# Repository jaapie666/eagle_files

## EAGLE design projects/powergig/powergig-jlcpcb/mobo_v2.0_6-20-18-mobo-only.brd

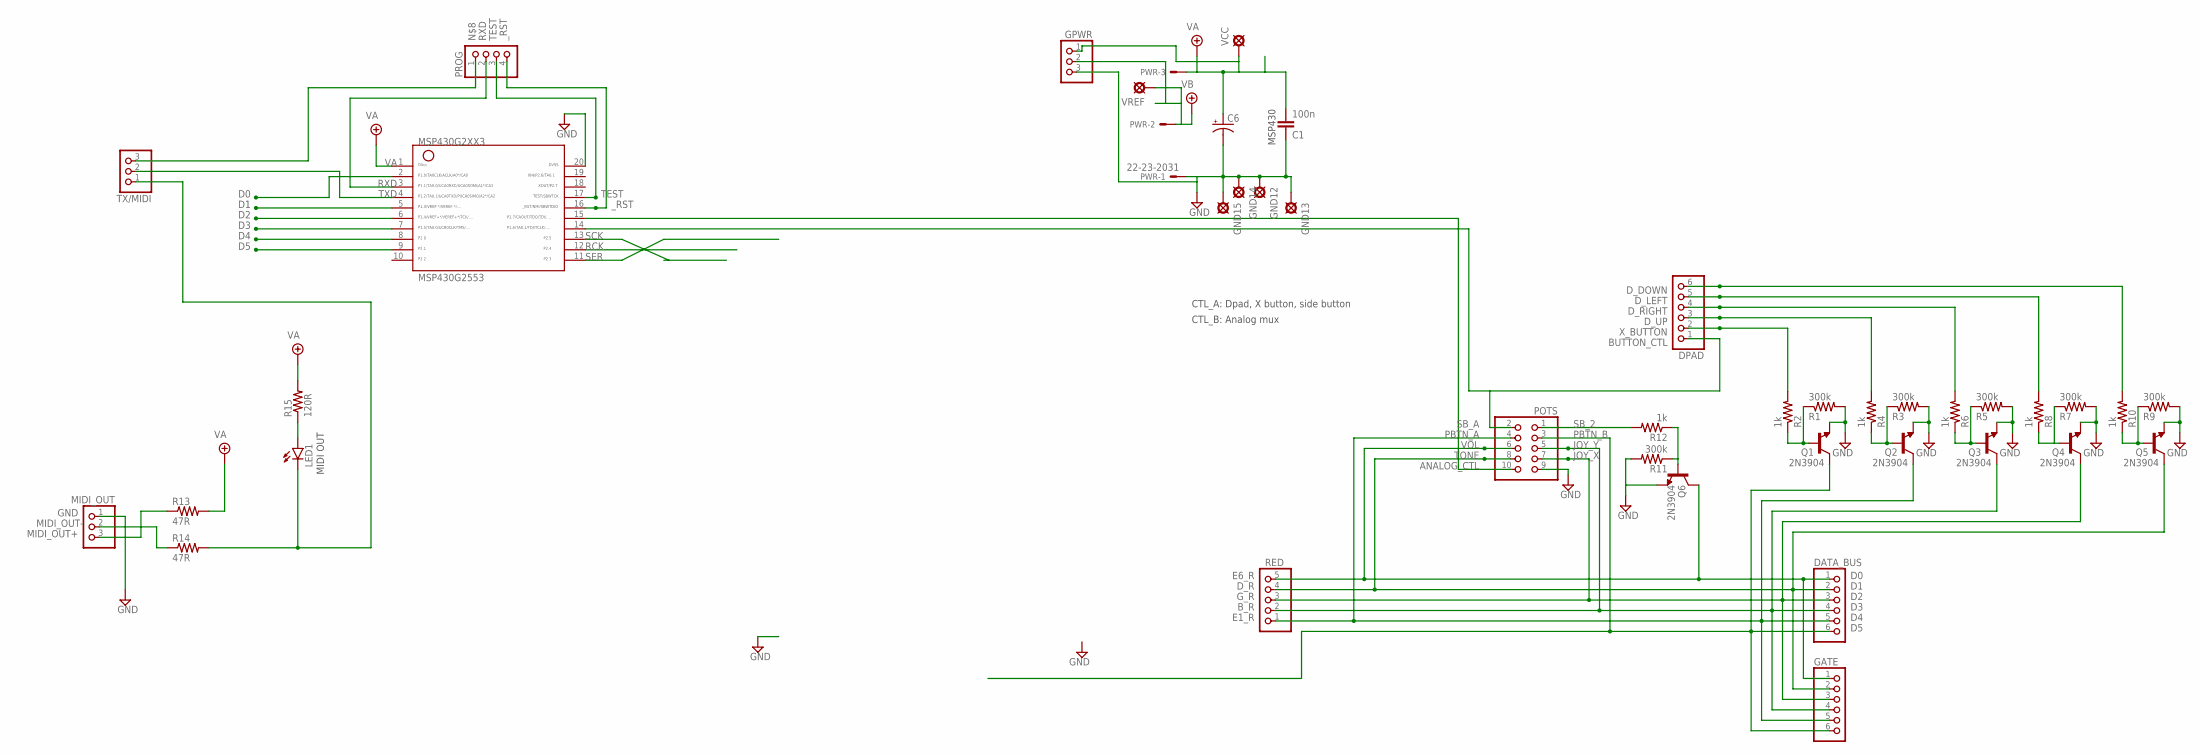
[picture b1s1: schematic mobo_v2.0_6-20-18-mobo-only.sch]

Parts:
C1: 100n; 050X030_050_3
C6: 0501; 050_020_1
DATA_BUS: PINHD-1X6; 1X06
DPAD: PINHD-1X6; 1X06
GATE: PINHD-1X6; 1X06
GND12, GND13, GND14, GND15: PAD; SQUARE
GPWR: PINHD-1X3; 1X03
LED1: LED3MM
MIDI_OUT: PINHD-1X3; 1X03
MSP430G2553: G2XX3---N20; N20
POTS: PINHD-2X5IDC; 10PIN_IDC
PROG: PINHD-1X4; 1X04
PWR: 22-23-2031
Q1, Q2, Q3, Q4, Q5, Q6: 2N3904; TO92-
R1, R3, R5, R7, R9, R11: 300k; R0207/3
R2, R4, R6, R8, R10, R12: 1k; R0207/3
R13, R14: 47R; R0207/3
R15: 120R; R0207/3
RED: PINHD-1X5; 1X05
TX/MIDI: PINHD-1X3; 1X03
VCC: PAD; SQUARE
VREF: PAD; SQUARE

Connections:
ANALOG_CTL: MSP430G2553.15, POTS.10
BUTTON_CTL: DPAD.1, MSP430G2553.14, POTS.2
D0: DATA_BUS.1, GATE.1, MSP430G2553.2, POTS.6, Q6.1 (C), RED.5
D1: DATA_BUS.2, GATE.2, MSP430G2553.5, POTS.8, Q5.1 (C), RED.4
D2: DATA_BUS.3, GATE.3, MSP430G2553.6, POTS.7, Q4.1 (C), RED.3
D3: DATA_BUS.4, GATE.4, MSP430G2553.7, POTS.5, Q3.1 (C), RED.2
D4: DATA_BUS.5, GATE.5, MSP430G2553.8, POTS.4, Q2.1 (C), RED.1
D5: DATA_BUS.6, GATE.6, MSP430G2553.9, POTS.3, Q1.1 (C)
D_DOWN: DPAD.6, R10.2
D_LEFT: DPAD.5, R8.2
D_RIGHT: DPAD.4, R6.2
D_UP: DPAD.3, R4.2
GND: C1.1, C6.-, GND12.1, GND13.1, GND14.1, GND15.1, GPWR.3, MIDI_OUT.1, MSP430G2553.20, POTS.9, PWR.1, Q1.3 (E), Q2.3 (E), Q3.3 (E), Q4.3 (E), Q5.3 (E), Q6.3 (E), R1.2, R3.2, R5.2, R7.2, R9.2, R11.2
MIDI_OUT+: MIDI_OUT.3, R13.1
MIDI_OUT-: MIDI_OUT.2, R14.1
unnamed: Q6.2 (B), R11.1, R12.1
unnamed: LED1.A, R15.1
unnamed: LED1.K (C), R14.2, TX/MIDI.1
unnamed: PROG.1, TX/MIDI.3
unnamed: Q1.2 (B), R1.1, R2.1
unnamed: Q2.2 (B), R3.1, R4.1
unnamed: Q3.2 (B), R5.1, R6.1
unnamed: Q4.2 (B), R7.1, R8.1
unnamed: Q5.2 (B), R9.1, R10.1
RCK: MSP430G2553.12
RXD: MSP430G2553.3, PROG.2
SB_2: POTS.1, R12.2
SCK: MSP430G2553.13
SER: MSP430G2553.11
TEST: MSP430G2553.17, PROG.3
TXD: MSP430G2553.4, TX/MIDI.2
VA: C1.2, C6.+, GPWR.1, MSP430G2553.1, PWR.3, R13.2, R15.2, VCC.1
VB: GPWR.2, PWR.2, VREF.1
X_BUTTON: DPAD.2, R2.2
_RST: MSP430G2553.16, PROG.4

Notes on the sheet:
MSP430
E6_R
D_R
G_R
B_R
E1_R
TONE
VOL
PBTN_A
PBTN_B
JOY_X
JOY_Y
SB_A
CTL_A: Dpad, X button, side button
CTL_B: Analog mux
MIDI OUT

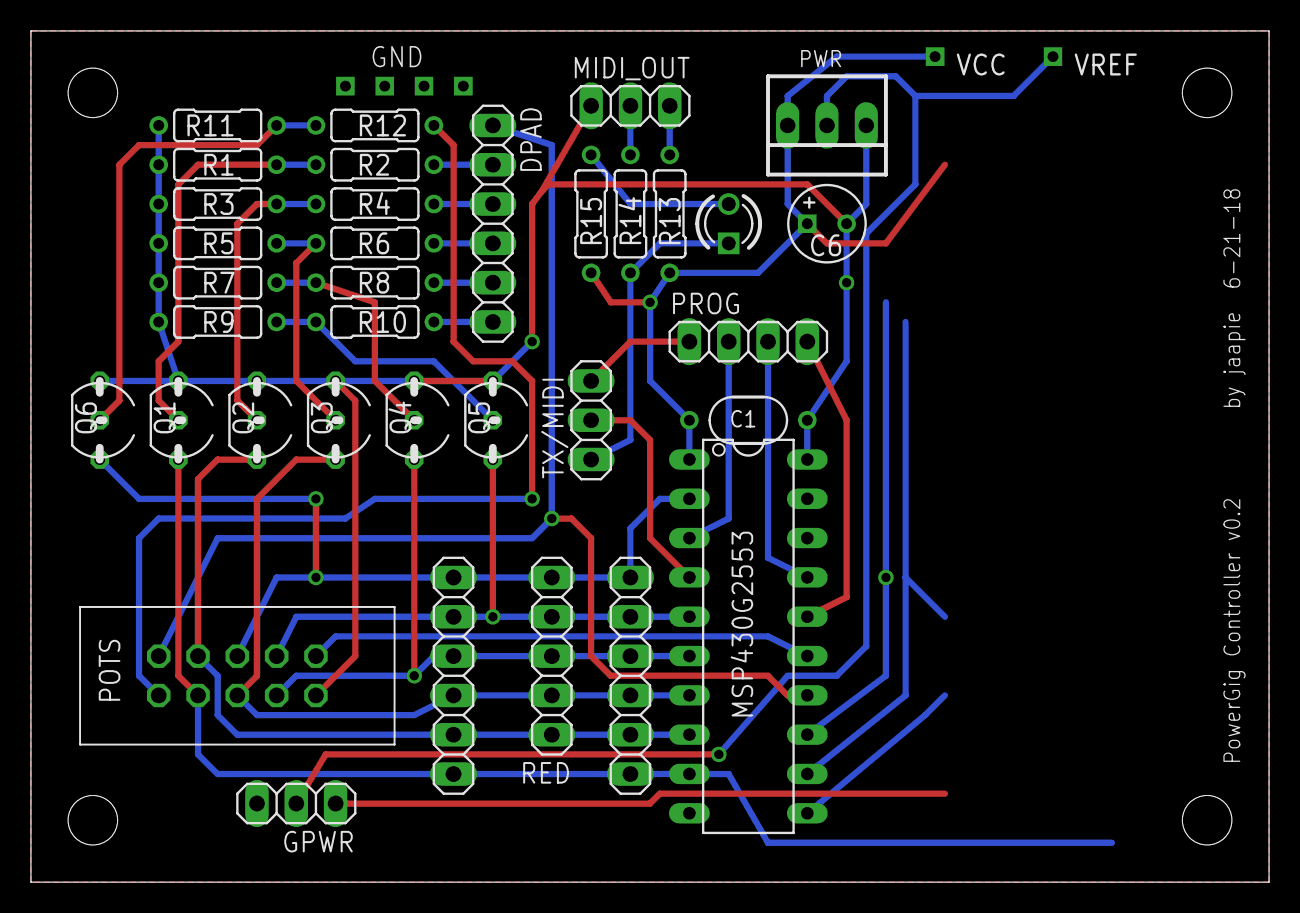
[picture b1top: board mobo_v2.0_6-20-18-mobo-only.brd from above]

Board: 2 copper layers, 80.0 x 55.0 mm, 41 parts (0 on the bottom side), 32 nets.

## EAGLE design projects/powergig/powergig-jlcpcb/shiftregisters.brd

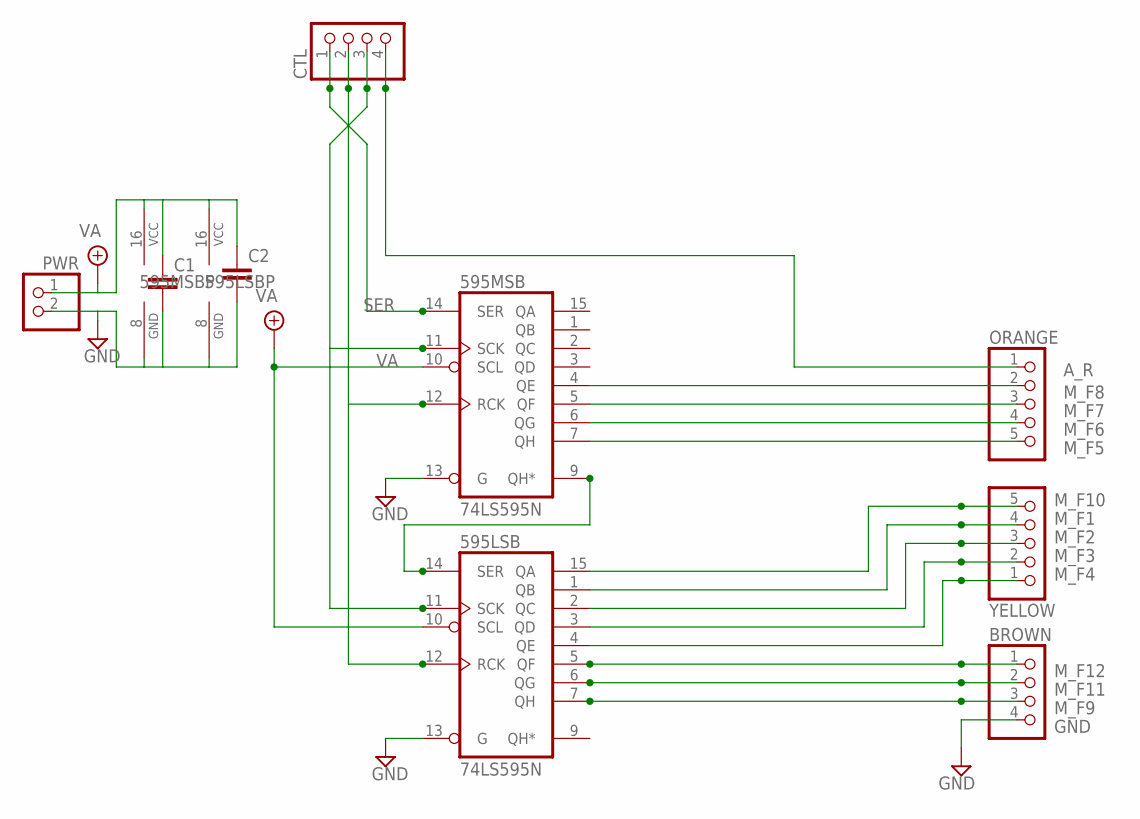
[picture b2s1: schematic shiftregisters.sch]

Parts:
595LSB, 595MSB: 74LS595N; DIL16
BROWN: PINHD-1X4; 1X04
C1, C2: 050X030_0251; 050X030_025
CTL: PINHD-1X4; 1X04
ORANGE: PINHD-1X5; 1X05
PWR: PINHD-1X2; 1X02
YELLOW: PINHD-1X5; 1X05

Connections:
D5: CTL.4, ORANGE.1
GND: 595LSB.8 (GND), 595LSB.13 (G), 595MSB.8 (GND), 595MSB.13 (G), BROWN.4, C1.2, C2.2, PWR.2
M_F1: 595LSB.1 (QB), YELLOW.4
M_F2: 595LSB.2 (QC), YELLOW.3
M_F3: 595LSB.3 (QD), YELLOW.2
M_F4: 595LSB.4 (QE), YELLOW.1
M_F5: 595MSB.7 (QH), ORANGE.5
M_F6: 595MSB.6 (QG), ORANGE.4
M_F7: 595MSB.5 (QF), ORANGE.3
M_F8: 595MSB.4 (QE), ORANGE.2
M_F9: 595LSB.7 (QH), BROWN.3
M_F10: 595LSB.15 (QA), YELLOW.5
M_F11: 595LSB.6 (QG), BROWN.2
M_F12: 595LSB.5 (QF), BROWN.1
unnamed: 595LSB.14 (SER), 595MSB.9 (QH*)
RCK: 595LSB.12 (RCK), 595MSB.12 (RCK), CTL.2
SCK: 595LSB.11 (SCK), 595MSB.11 (SCK), CTL.3
SER: 595MSB.14 (SER), CTL.1
VA: 595LSB.10 (SCL), 595LSB.16 (VCC), 595MSB.10 (SCL), 595MSB.16 (VCC), C1.1, C2.1, PWR.1

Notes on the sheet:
A_R

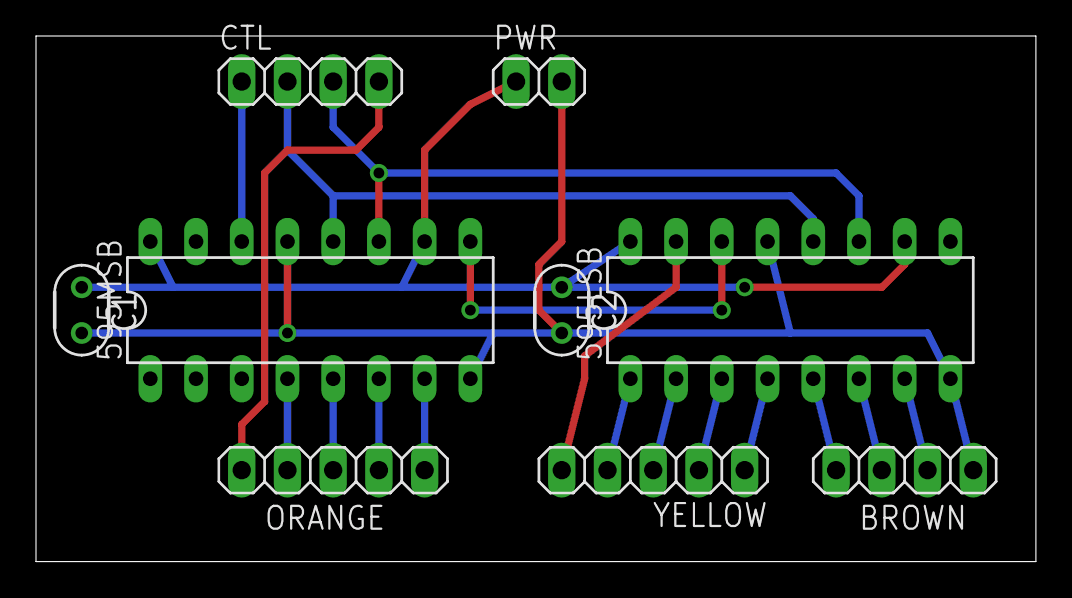
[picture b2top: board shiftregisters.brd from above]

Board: 2 copper layers, 55.5 x 29.2 mm, 9 parts (0 on the bottom side), 19 nets.

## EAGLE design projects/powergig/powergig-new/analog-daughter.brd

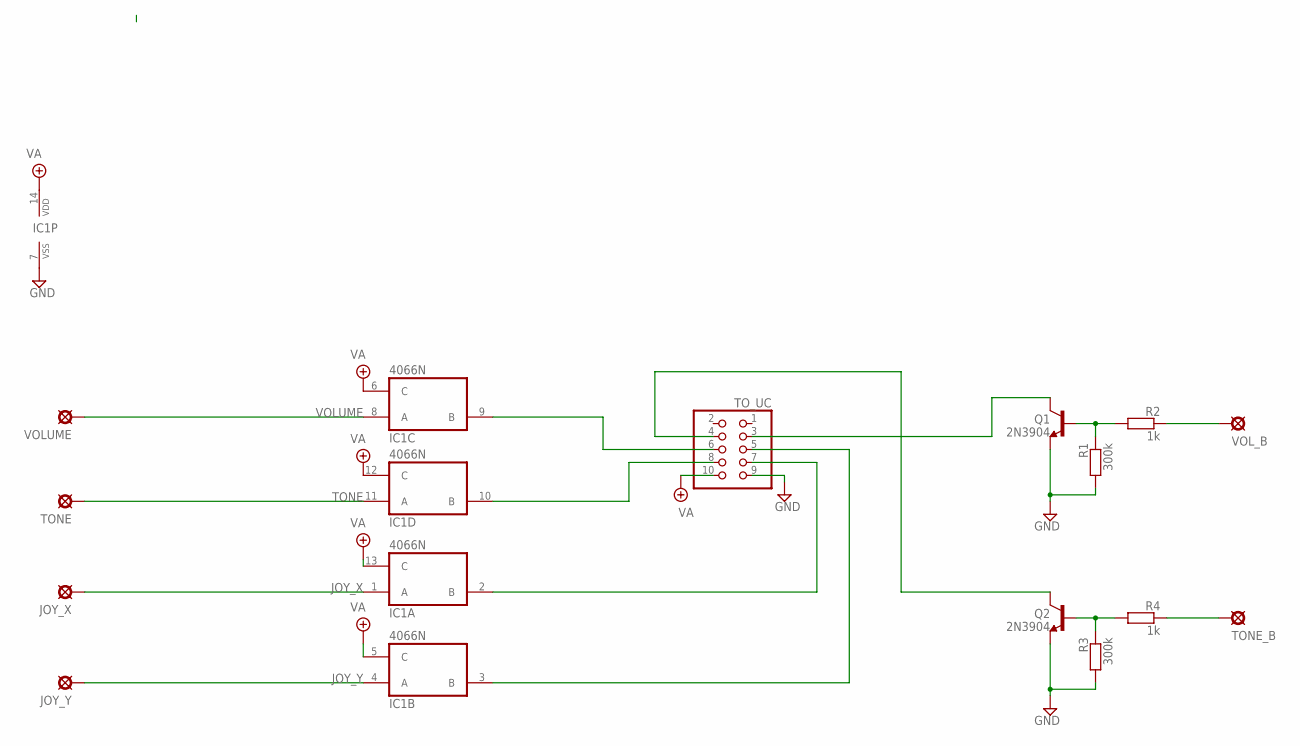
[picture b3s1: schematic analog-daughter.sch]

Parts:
IC1: 4066N; DIL14
JOY_X: PAD; SQUARE
JOY_Y: PAD; SQUARE
Q1, Q2: 2N3904; TO92-
R1, R3: 300k; R0207/1V
R2, R4: 1k; R0207/1V
TONE: PAD; SQUARE
TONE_B: PAD; SQUARE
TO_UC: PINHD-2X5; 2X05
VOLUME: PAD; SQUARE
VOL_B: PAD; SQUARE

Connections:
GND: IC1.7 (VSS), Q1.3 (E), Q2.3 (E), R1.2, R3.2, TO_UC.9
JOY_X: IC1.1 (A), JOY_X.1
JOY_Y: IC1.4 (A), JOY_Y.1
unnamed: Q1.1 (C), TO_UC.3
unnamed: IC1.9 (B), TO_UC.6
unnamed: IC1.10 (B), TO_UC.8
unnamed: IC1.2 (B), TO_UC.7
unnamed: IC1.3 (B), TO_UC.5
unnamed: Q2.1 (C), TO_UC.4
unnamed: Q1.2 (B), R1.1, R2.2
unnamed: Q2.2 (B), R3.1, R4.2
TONE: IC1.11 (A), TONE.1
TONE_BUTTON: R4.1, TONE_B.1
VA: IC1.5 (C), IC1.6 (C), IC1.12 (C), IC1.13 (C), IC1.14 (VDD), TO_UC.10
VOLUME: IC1.8 (A), VOLUME.1
VOL_BUTTON: R2.1, VOL_B.1

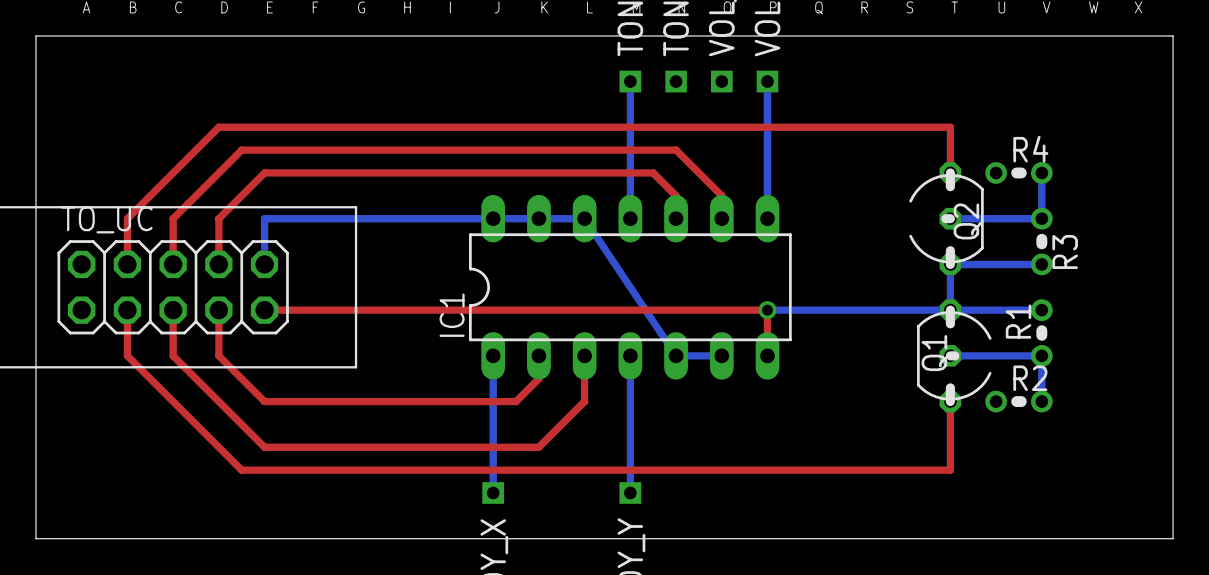
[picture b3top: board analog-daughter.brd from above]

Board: 2 copper layers, 63.2 x 27.9 mm, 14 parts (0 on the bottom side), 16 nets.

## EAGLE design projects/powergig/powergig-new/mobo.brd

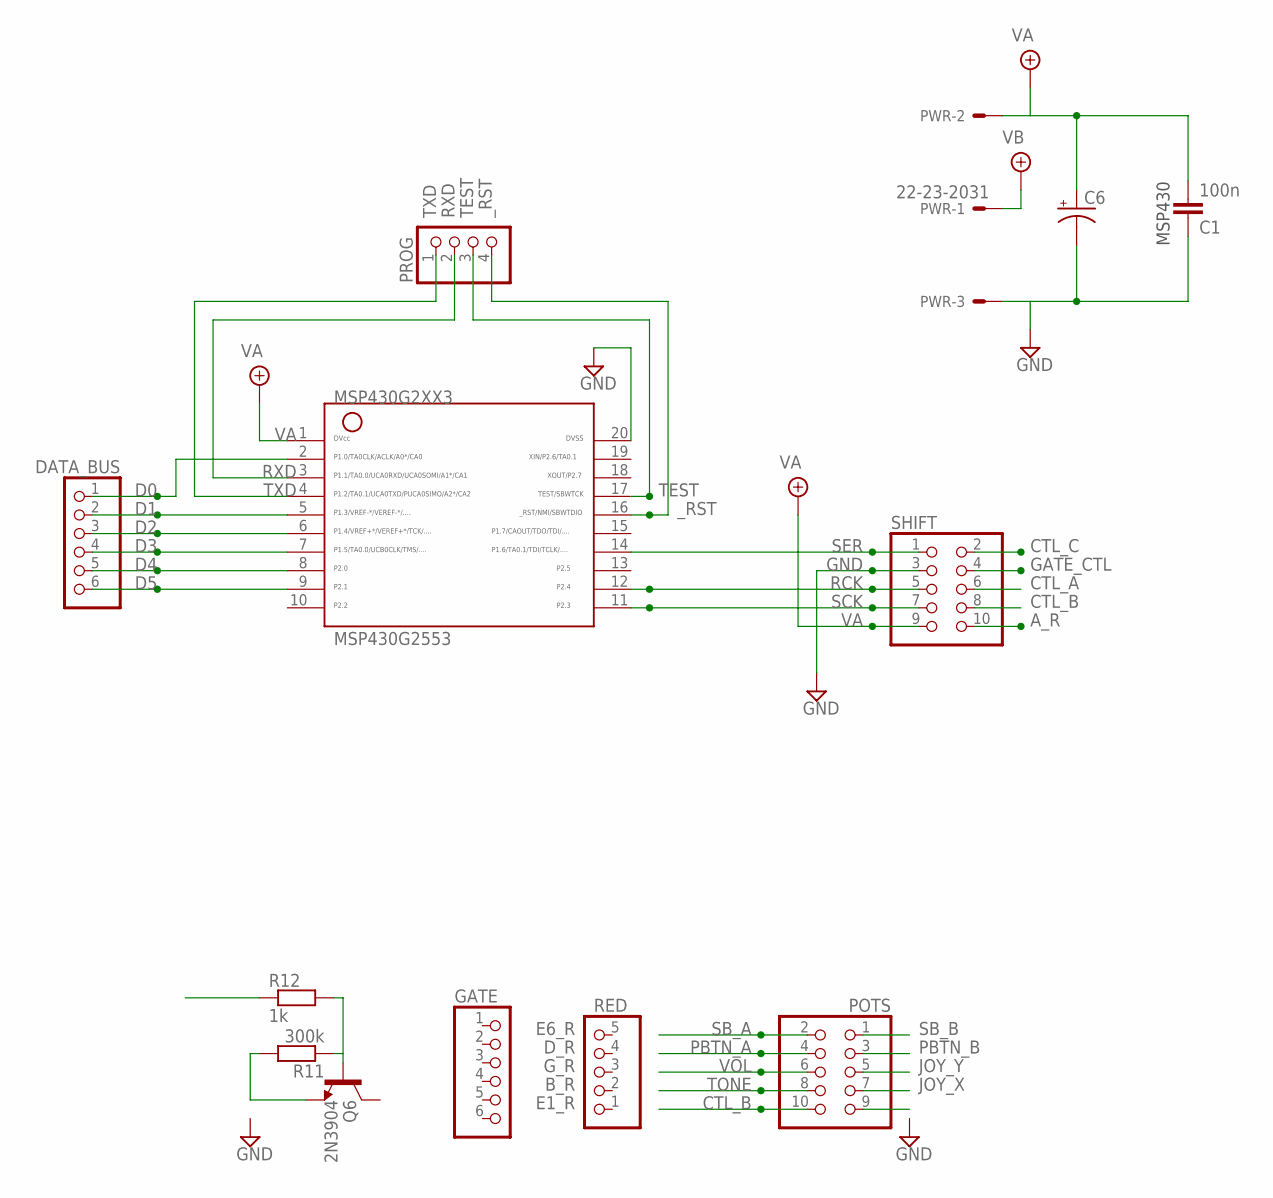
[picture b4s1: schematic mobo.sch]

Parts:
C1: 100n; 050X030_050_3
C6: 0501; 050_020_1
DATA_BUS: PINHD-1X6; 1X06
GATE: PINHD-1X6; 1X06
MSP430G2553: G2XX3---N20; N20
POTS: PINHD-2X5; 2X05
PROG: PINHD-1X4; 1X04
PWR: 22-23-2031
Q6: 2N3904; TO92-
R11: 300k; R0207/1V
R12: 1k; R0207/1V
RED: PINHD-1X5; 1X05
SHIFT: PINHD-2X5; 2X05

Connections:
CTL_A: SHIFT.6
CTL_B: SHIFT.8
CTL_C: SHIFT.2
D0: DATA_BUS.1, MSP430G2553.2, SHIFT.10
D1: DATA_BUS.2, MSP430G2553.5
D2: DATA_BUS.3, MSP430G2553.6
D3: DATA_BUS.4, MSP430G2553.7
D4: DATA_BUS.5, MSP430G2553.8
D5: DATA_BUS.6, MSP430G2553.9
GATE_CTL: SHIFT.4
GND: C1.1, C6.-, MSP430G2553.20, PWR.3, SHIFT.3
unnamed: Q6.2 (B), R11.1, R12.2
unnamed: Q6.3 (E), R11.2
RCK: MSP430G2553.12, SHIFT.5
RXD: MSP430G2553.3, PROG.2
SB_2: R12.1
SCK: MSP430G2553.11, SHIFT.7
SER: MSP430G2553.14, SHIFT.1
TEST: MSP430G2553.17, PROG.3
TXD: MSP430G2553.4, PROG.1
VA: C1.2, C6.+, MSP430G2553.1, PWR.2, SHIFT.9
VB: PWR.1
_RST: MSP430G2553.16, PROG.4

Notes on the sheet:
MSP430
A_R
E6_R
D_R
G_R
B_R
E1_R
TONE
VOL
PBTN_A
PBTN_B
JOY_X
JOY_Y
SB_A
CTL_B
SB_B

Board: 2 copper layers, 13 parts (0 on the bottom side), 17 nets, no tracks yet.

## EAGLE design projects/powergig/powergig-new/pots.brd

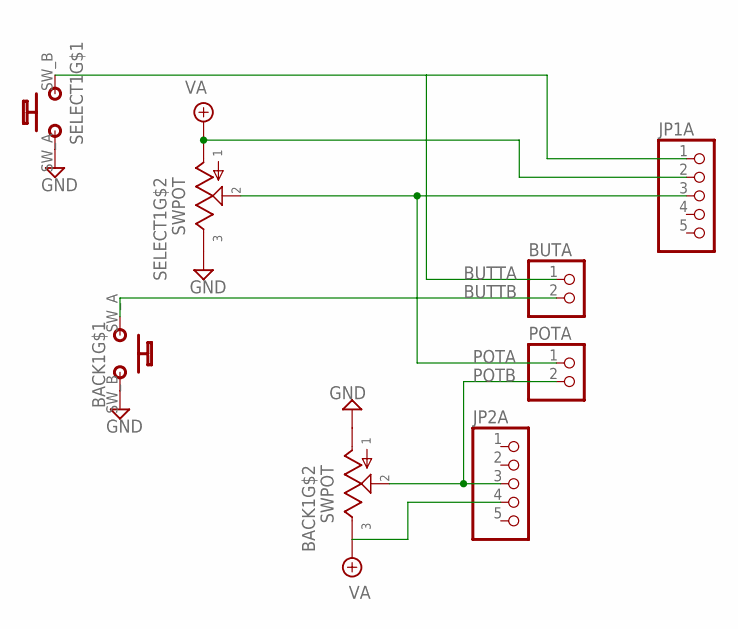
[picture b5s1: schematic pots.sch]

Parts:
BACK1: SWPOT
BUTA: PINHD-1X2; 1X02
JP1A, JP2A: PINHD-1X5; 1X05
POTA: PINHD-1X2; 1X02
SELECT1: SWPOT

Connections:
BUTTA: BUTA.1, JP1A.1, SELECT1.SW_B (B_B)
BUTTB: BACK1.SW_A (B_A), BUTA.2
GND: BACK1.POT_B, BACK1.SW_B (B_B), SELECT1.POT_A, SELECT1.SW_A (B_A)
POTA: JP1A.3, POTA.1, SELECT1.POT_W
POTB: BACK1.POT_W, JP2A.3, POTA.2
VA: BACK1.POT_A, JP1A.2, JP2A.4, SELECT1.POT_B

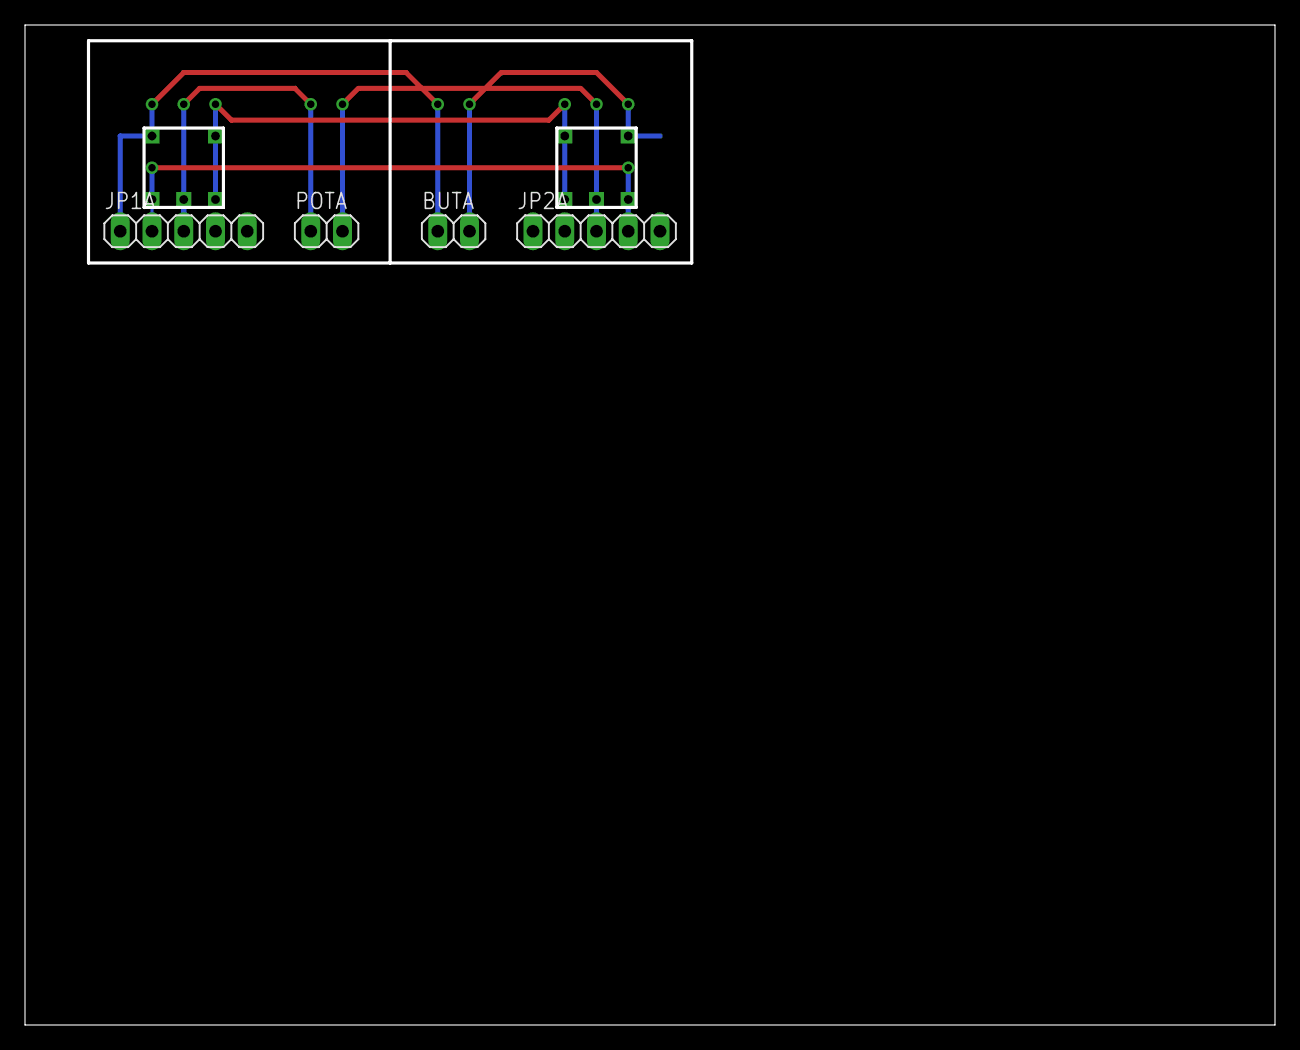
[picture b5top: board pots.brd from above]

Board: 2 copper layers, 100.0 x 80.0 mm, 6 parts (0 on the bottom side), 6 nets.
